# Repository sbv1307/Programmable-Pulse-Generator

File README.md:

# Programmable pulse generator for Arduino.
 The sketch will be build for Arduino NANO 

 The Programmable Pulse Generate will generate pulses on a number of output pins.

 ## Programming
 The Programmable Pulse Generate uses a REST approch over the serial connection (see below). 

  Programmeable parameters:
 - Number of output pins (with a maximum of 10).
 - Puls length in millis for each channel.
 - Puls period in millis for each channel.<span id="a1">[[1]](#f1)</span>
 - The pause between pulses in each channel "Pulse Order Interval".
 - Relation between pulses on the various channels (pulseOrder). 
   - Individual     'I' Pulses starts Simultaneously, but act upon their own pulse length and interval. (Default)
   - Simultaneously 'S' All pulses starts a the same time. Pulse interval is redefined to be the lognest pulse length plus the longest pulse interval.
   - Sequential     'Q' Pulses starts after another), with a programmable pause between the pulses (Pulse Order Interval). 
   - Randum         'R' Pulses starts randumly om each channel and follow their own length and interval.
 - The pulse length on each channel can be selected as LOW pulse or HIGH pulse.
 - Number of pulses fired on each channel. Initiated by a push button function attached to pin A5 (19).
   When the push button is pressed once, the pulse generator stops.
   When the push button is pressed twice, the pulse generator restarts, at fires the configured pulses on each channel.
   When the push button is pressed once, after it has been pushed twice, the pusle generator restarts and runs infinitly.
   
 ### **Firmware Version histoty:**
 * 1.2.4 - Bugfix: Cannot set pulseLength. [if ( value = 0 ... changed to  if ( value >= 0 ...] Value would never be zero:-)
 * 1.2.3 - Bugfix in Sequencial run and documentatino update
 * 1.2.2 - Parameter for programmelable delay after "Run Infinite" to "Run Limited"
 * 1.2.1 - Issues regarding configurations being changed, when Puls Order is changed from I to Q, S or R. handleRest() si change to reload the stored configuration, before adding changes.
 * 1.2.0 - Configuration bugfixes
 * 1.1.2 - Minor documentation corrections - No funktional changes

 * 1.1.0 - Adding push button funktionality, which will fire a configured number of pulses on each channel.
 * 1.0.0 - Prod. version.
 * 0.2.0 - Versions 0.2.x is for developing Programmable interface.
         - Taking the REST approch for programming parameters. 
 * 0.1.1 - Building in funktionality for handeling different "pulse orders".
         - pinState re-defined to match ACTIVE / PASSIVE pulse instead of LOW / HIGH.
 * 0.1.0 - Initial commit: Basic funktionalites are build in. No parameters are programmable, but the required program structure is in place.

#### REST Approch
 * Communication will be over serial connection (USB).
 * When not connected, the sketch will start, using the last programmed configuration.

/configurations/{parameret}/{id}/{value} or /configurations/{parameret}/{value} 

                <numberOfChannels>  /<1 - 10> 
                <pulseOrder>        /<I, S, Q or R>
                <pulseOrderInterval>/<millisecunds>
                <pulseLength>       /<channel 1-10>/<millisecunds>
                <pulsePeriod>       /<channel 1-10>/<millisecunds>
                <pulseActive>       /<channel 1-10>/<LOW or HIGH>
                <numberOfPulses>    /<channel 1-10>/<1 - 100000>
                setDefaults

 ##### Configuration examaples:
 * configurations/numberOfChannels/3
 * configurations/pulseOrder/S
 * configurations/pulseOrderInterval/250
 * configurations/pulseLength/1/100
 * configurations/pulsePeriod/1/500<span id="a1">[[1]](#f1)</span>
 * configurations/pulseActive/1/HIGH
 * configurations/numberOfPulses/1/1000
 * configurations/setDefaults

##### Ardhino nano Pin definition/layout:***
 * Pin  0: Serial RX
 * Pin  1: Serial TX
 * Pin  2: Channel pin 1:
 * Pin  3: Channel pin 2: 
 * Pin  4: Channel pin 3:
 * Pin  5: Channel pin 4:
 * Pin  6: Channel pin 5:
 * Pin  7: Channel pin 6:
 * Pin  8: Channel pin 7:
 * Pin  10: Channel pin 9:
 * Pin  11: Channel pin 10:
 * Pin  12: Channel pin 11:
 * Pin  13: LED_BUILTIN. 
 * Pin  14: (A0): RANDUM_SEED_PIN    Used for randumSeed() to generate different seed numbers each time the sketch runs.
 * Pin  15: (A1): N/C
 * Pin  16: (A2): N/C
 * Pin  17: (A3): N/C
 * Pin  18: (A4): N/C
 * Pin  19: (A5): Button pin. Button to running in non continoougious mode (file configured numer of pulses)

### Project eligibility. 
The sketch was build for simulating the pulses on the open collector outputs on a number of Carlo Gavazzi energy meters Type EM23 DIN and Type EM111.
The project "EnergyRegistgration", which are build to register pulses on the open collector output on the above mentined meters has a problem, counting the pulses corectly. Some pulses are rigistered but not counted and some are counted too many.
This project is to investigate into this problem.

##### 1. <span id="f1"></span>Note: If pulseOrder is set to 'Q', puls period on channel 1 will define the pause from the last puls in the sequence to the first starts. 

### **Project Version History:**
2.0.0 - Hardware merged with Firmware (initial product version)

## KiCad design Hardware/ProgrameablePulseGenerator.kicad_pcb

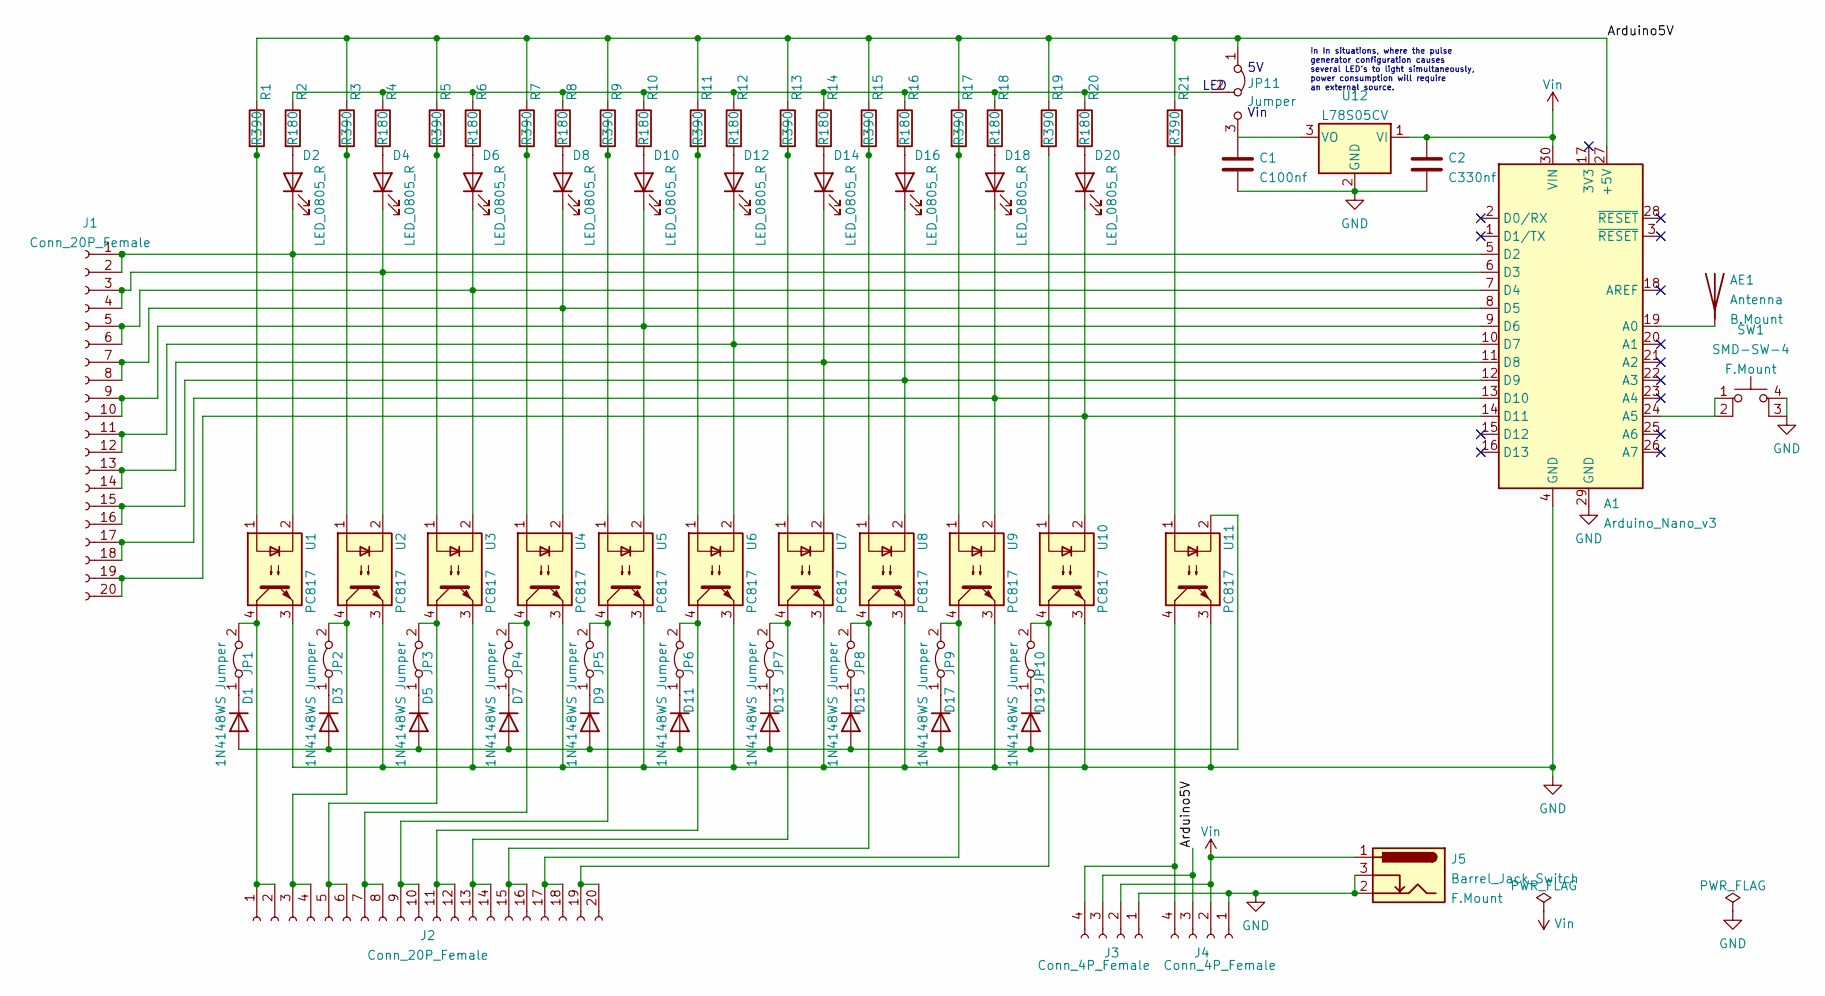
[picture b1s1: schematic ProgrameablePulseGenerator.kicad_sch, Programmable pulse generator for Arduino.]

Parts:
A1: Arduino_Nano_v3; Arduino_Nano; MFR. Part # A000005; Digi-Key Part # 1050-1001-ND
AE1: Antenna; Undefined_Antenna(B.Mount)
C1: C100nf; C_0402_1005Metric; MFR. Part # CL05B104KO5NNNC; JLCPCB Part # C1525
C2: C330nf; C_0805_2012Metric; MFR. Part # 0805B334K500NT; JLCPCB Part # C1740
D1, D3, D5, D7, D9, D11, D13, D15, D17, D19: 1N4148WS; D_SOD-323F; MFR. Part # 1N4148WS; JLCPCB Part # C2128
D2, D4, D6, D8, D10, D12, D14, D16, D18, D20: LED_0805_R; LED_0805_2012Metric; MFR. Part # NCD0805R1; JLCPCB Part # C84256
J1, J2: Conn_20P_Female; PinHeader_1x20_P2.54mm_Vertical; MFR. Part # 4155; Digi-Key Part # 1528-2927-ND
J3, J4: Conn_4P_Female; PinHeader_1x04_P2.54mm_Vertical; MFR. Part # 4155; Digi-Key Part # 1528-2927-ND
J5: Barrel_Jack_Switch; BarrelJack_Horizontal(F.Mount); MFR. Part # PJ-058AH; Digi-Key Part # CP-058AH-ND
JP1, JP2, JP3, JP4, JP5, JP6, JP7, JP8, JP9, JP10: Jumper; SolderJumper-2_P1.3mm_Bridged_RoundedPad1.0x1.5mm(B.Mount)
JP11: Jumper; PinHeader_1x03_P2.54mm_Vertical
R1, R3, R5, R7, R9, R11, R13, R15, R17, R19, R21: R390; R_0603_1608Metric; MFR. Part # 0603WAF3900T5E; JLCPCB Part # C23151
R2, R4, R6, R8, R10, R12, R14, R16, R18, R20: R180; R_0805_2012Metric; MFR. Part # 0805W8F1800T5E; JLCPCB Part # C25270
SW1: SMD-SW-4; SW_Tactile_Straight_(F.Mount); MFR. Part # TS-1187A-B-A-B; JLCPCB Part # C318884
U1, U2, U3, U4, U5, U6, U7, U8, U9, U10, U11: PC817; DIP-4_W7.62mm_Slim
U12: L78S05CV; TO-220-3_Vertical; MFR. Part # L78S05CV; Digi-Key Part # 497-1468-5-ND

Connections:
/Arduino5V: A1.27 (+5V), J3.3, J4.3, JP11.1 (A), R1.1, R3.1, R5.1, R7.1, R9.1, R11.1, R13.1, R15.1, R17.1, R19.1, R21.1
GND: A1.4 (GND), A1.29 (GND), C1.2, C2.2, J3.1, J4.1, J5.2, J5.3, SW1.3 (K), SW1.4 (A), U1.3, U2.3, U3.3, U4.3, U5.3, U6.3, U7.3, U8.3, U9.3, U10.3, U11.3, U12.2 (GND)
unnamed: A1.5 (D2), D2.1 (K), J1.1, J1.2, U1.2
unnamed: A1.6 (D3), D4.1 (K), J1.3, J1.4, U2.2
unnamed: A1.7 (D4), D6.1 (K), J1.5, J1.6, U3.2
unnamed: A1.8 (D5), D8.1 (K), J1.7, J1.8, U4.2
unnamed: A1.9 (D6), D10.1 (K), J1.9, J1.10, U5.2
unnamed: A1.10 (D7), D12.1 (K), J1.11, J1.12, U6.2
unnamed: A1.11 (D8), D14.1 (K), J1.13, J1.14, U7.2
unnamed: A1.12 (D9), D16.1 (K), J1.15, J1.16, U8.2
unnamed: A1.13 (D10), D18.1 (K), J1.17, J1.18, U9.2
unnamed: A1.14 (D11), D20.1 (K), J1.19, J1.20, U10.2
unnamed: A1.19 (A0), AE1.1 (A)
unnamed: A1.24 (A5), SW1.1, SW1.2
unnamed: C1.1, JP11.3 (B), U12.3 (VO)
unnamed: D1.1 (K), JP1.1 (A)
unnamed: D1.2 (A), D3.2 (A), D5.2 (A), D7.2 (A), D9.2 (A), D11.2 (A), D13.2 (A), D15.2 (A), D17.2 (A), D19.2 (A), U11.2
unnamed: D2.2 (A), R2.2
unnamed: D3.1 (K), JP2.1 (A)
unnamed: D4.2 (A), R4.2
unnamed: D5.1 (K), JP3.1 (A)
unnamed: D6.2 (A), R6.2
unnamed: D7.1 (K), JP4.1 (A)
unnamed: D8.2 (A), R8.2
unnamed: D9.1 (K), JP5.1 (A)
unnamed: D10.2 (A), R10.2
unnamed: D11.1 (K), JP6.1 (A)
unnamed: D12.2 (A), R12.2
unnamed: D13.1 (K), JP7.1 (A)
unnamed: D14.2 (A), R14.2
unnamed: D15.1 (K), JP8.1 (A)
unnamed: D16.2 (A), R16.2
unnamed: D17.1 (K), JP9.1 (A)
unnamed: D18.2 (A), R18.2
unnamed: D19.1 (K), JP10.1 (A)
unnamed: D20.2 (A), R20.2
unnamed: J2.1, J2.2, JP1.2 (B), U1.4
unnamed: J2.3, J2.4, JP2.2 (B), U2.4
unnamed: J2.5, J2.6, JP3.2 (B), U3.4
unnamed: J2.7, J2.8, JP4.2 (B), U4.4
unnamed: J2.9, J2.10, JP5.2 (B), U5.4
unnamed: J2.11, J2.12, JP6.2 (B), U6.4
unnamed: J2.13, J2.14, JP7.2 (B), U7.4
unnamed: J2.15, J2.16, JP8.2 (B), U8.4
unnamed: J2.17, J2.18, JP9.2 (B), U9.4
unnamed: J2.19, J2.20, JP10.2 (B), U10.4
unnamed: J3.4, J4.4, U11.4
unnamed: JP11.2 (C), R2.1, R4.1, R6.1, R8.1, R10.1, R12.1, R14.1, R16.1, R18.1, R20.1
unnamed: R1.2, U1.1
unnamed: R3.2, U2.1
unnamed: R5.2, U3.1
unnamed: R7.2, U4.1
unnamed: R9.2, U5.1
unnamed: R11.2, U6.1
unnamed: R13.2, U7.1
unnamed: R15.2, U8.1
unnamed: R17.2, U9.1
unnamed: R19.2, U10.1
unnamed: R21.2, U11.1
Vin: A1.30 (VIN), C2.1, J3.2, J4.2, J5.1, U12.1 (VI)

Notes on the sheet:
LED
In In situations, where the pulse generator configuration causes several LED's to light simultaneously, power consumption will require an external source.
Vin

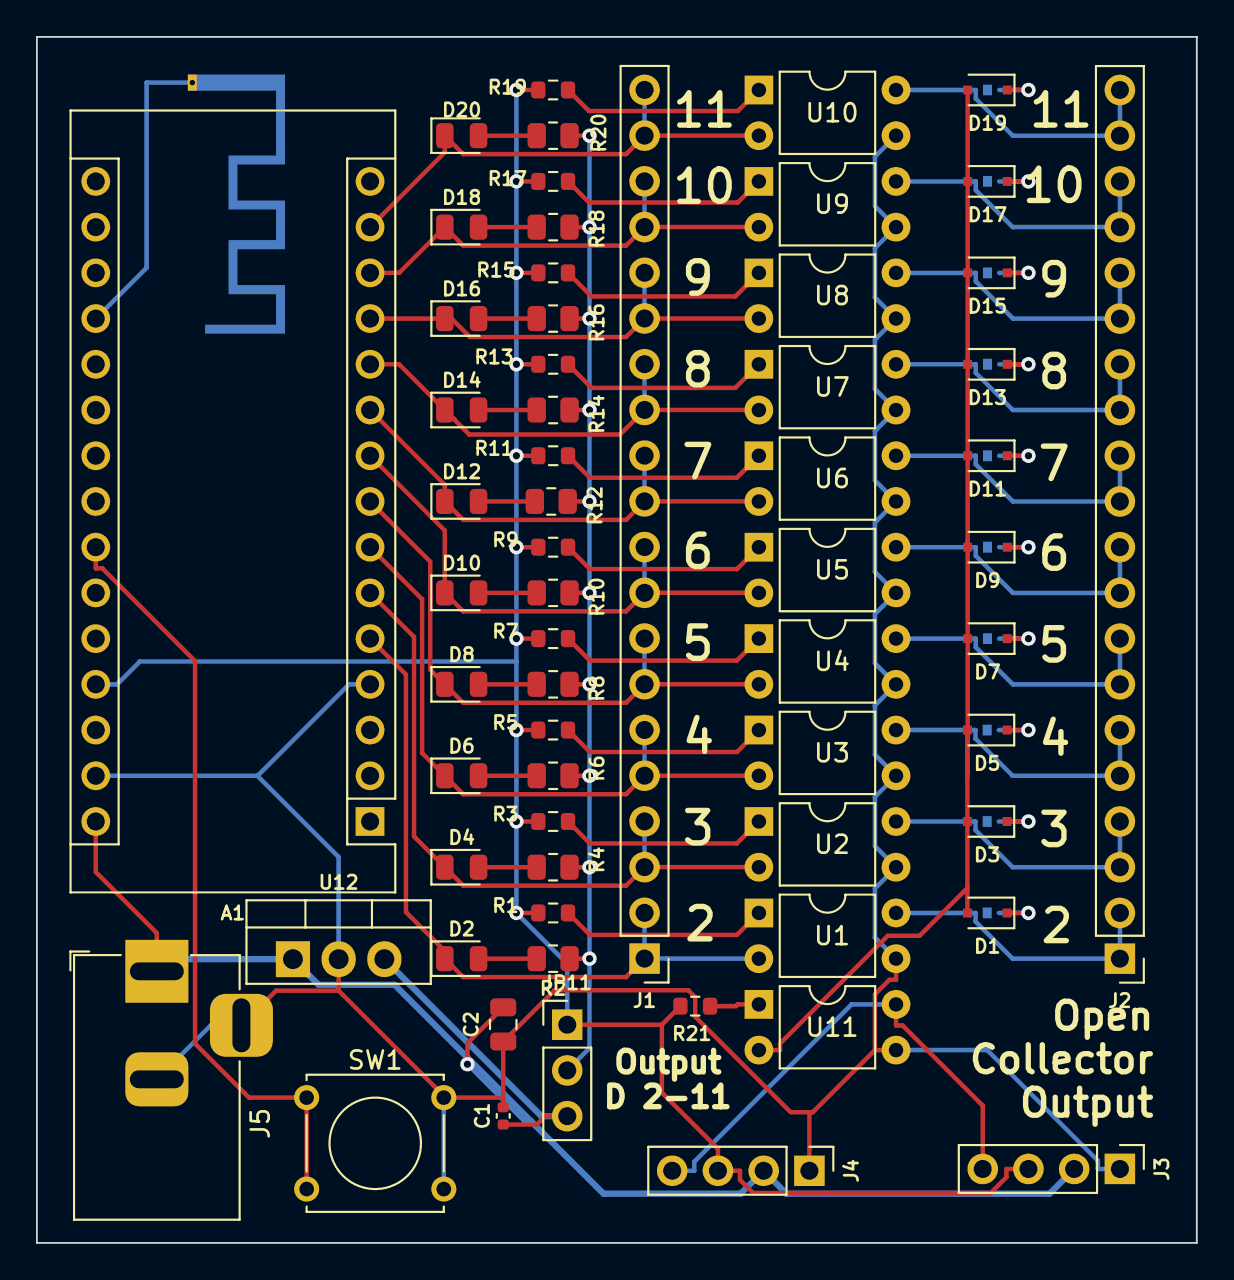
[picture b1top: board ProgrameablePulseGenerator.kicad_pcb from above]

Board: 2 copper layers, 64.4 x 67.0 mm, 74 parts (0 on the bottom side), 60 nets.

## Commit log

2020-12-06 Initial commit - moving project
2020-12-06 * 0.1.1 - Building in funktionality for handeling different "pulse orders".
2020-12-06 Final changes for Version V0.1.1
2020-12-06 * 0.2.0 - Versions 0.2.x is for developing Programmable interface.
2020-12-06 * 1.0.0 - Prod. version.
2020-12-10 * 1.1.0 - Adding push button funktionality, which will fire a configured number of pulses on each channel.
2021-02-06 1.1.1 - Documentation update - No funktional changes
2021-12-12 EEPROMAnything.h added
2021-12-31 minor documentation corrrections
2021-12-31 bugfixes
2022-01-01 handleRest enhangements
2022-01-01 Config enhangements
2022-01-27 Ver. 1.2.3 - Sequential bug fixes and documentation updates
2022-01-27 none
2022-01-27 Ver 1.2.3
2022-01-27 Tag update
2022-02-15 Bugfix: Could not set pulse length
2022-02-15 Empty commit
2022-03-30 VS Code vorking files removed from git
2022-03-30 Arduino files replaced and .gitignore updated to manage future Arduinio and KiCad working files
2022-03-30 Initial commit for rearagen and HW add on
2022-03-30 submodule added
2022-03-31 Library updated
2022-04-05 Hardware merged with Firmware (initial product version)
2024-08-23 DOC: PDF documentation files added
